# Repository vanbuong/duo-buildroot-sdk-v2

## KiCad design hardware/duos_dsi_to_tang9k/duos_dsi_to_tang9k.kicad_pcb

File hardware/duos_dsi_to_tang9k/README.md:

# Duo S MIPI DSI -> Tang Nano 9K

Generated by `gen_project.py` (re-run to regenerate). Open `duos_dsi_to_tang9k.kicad_pro` in KiCad 7+.
Network diagram: `dphy_full_lp_network.png`.

## Connectors
- **J1** = Duo S CON26A (2x13). pair0=D0 (1/3), pair1=D1 (2/4), pair2=CLK (7/9); D2/D3 unused.
- **J2** mirrors Tang Nano 9K header J6 (pin n = pin n), **J3** mirrors header J5.

| Signal | Tang pin | Header pin | Bank/IO |
|---|---|---|---|
| HS_CK_P / N | 80 / 79 | J6-8 / J6-9 | IOT12A/B, 1.8 V LVDS |
| HS_D0_P / N | 82 / 81 | J6-6 / J6-7 | IOT11A/B, 1.8 V LVDS |
| HS_D1_P / N | 84 / 83 | J6-4 / J6-5 | IOT10A/B, 1.8 V LVDS |
| LP_D0_P | 85 | J6-3 | IOT8B, 1.8 V LVCMOS |
| LP_CK_P (via level shifter) | 25 | J5-5 | IOB8A, 3.3 V |
| LP_D1_P (via level shifter) | 26 | J5-6 | IOB8B, 3.3 V |

J2 pin 23 = GND and pin 24 = 3V3 are used for the level shifters and VCM bias.

## Receive network (per lane)
- 2x50R + 100nF split termination: 100R differential at HS, DC-open so LP levels are not loaded.
- HS AC-coupled (100nF) to the LVDS pair, biased to VCM 0.9 V (27k/10k divider from 3V3).
- 470R LP tap from DSI_x_P. CK and D1 go through SN74AUP1T17 (3.3 V supply) to the 3.3 V pins; D0 goes straight to pin 85.
- 2-layer, 0.8 mm, GND pour on B.Cu; `DSI_*`/`HS_*` are in net class MIPI_DPHY_100R (0.25/0.2 mm starting values - verify).

## Must verify before fab
1. SN74AUP1T17: check the datasheet that VT+ (max) at VCC=3.3 V is below the D-PHY LP-high level (>= 0.88 V RX spec). Pick another low-threshold part if not.
2. `ROW_PITCH` (J2<->J3 spacing, 17.78 mm assumed) and pin-1 orientation vs your Tang Nano 9K. Use female sockets.
3. Confirm in the Gowin pin list that IOT10/11/12 A/B are true LVDS _T/_C pairs and that LVDS input at 1.8 V VCCO with 0.9 V common mode is allowed.
4. Lane map matches the SDK 2-lane panel config {LANE_0, LANE_1, LANE_CLK}; swap `lane_pn_swap` in `cvi_mpi/component/panel/cv181x/*.h` if routing ends up crossed.
5. Generated without KiCad available: open, run ERC/DRC (expect 3V3/GND power-flag warnings), route, re-save.

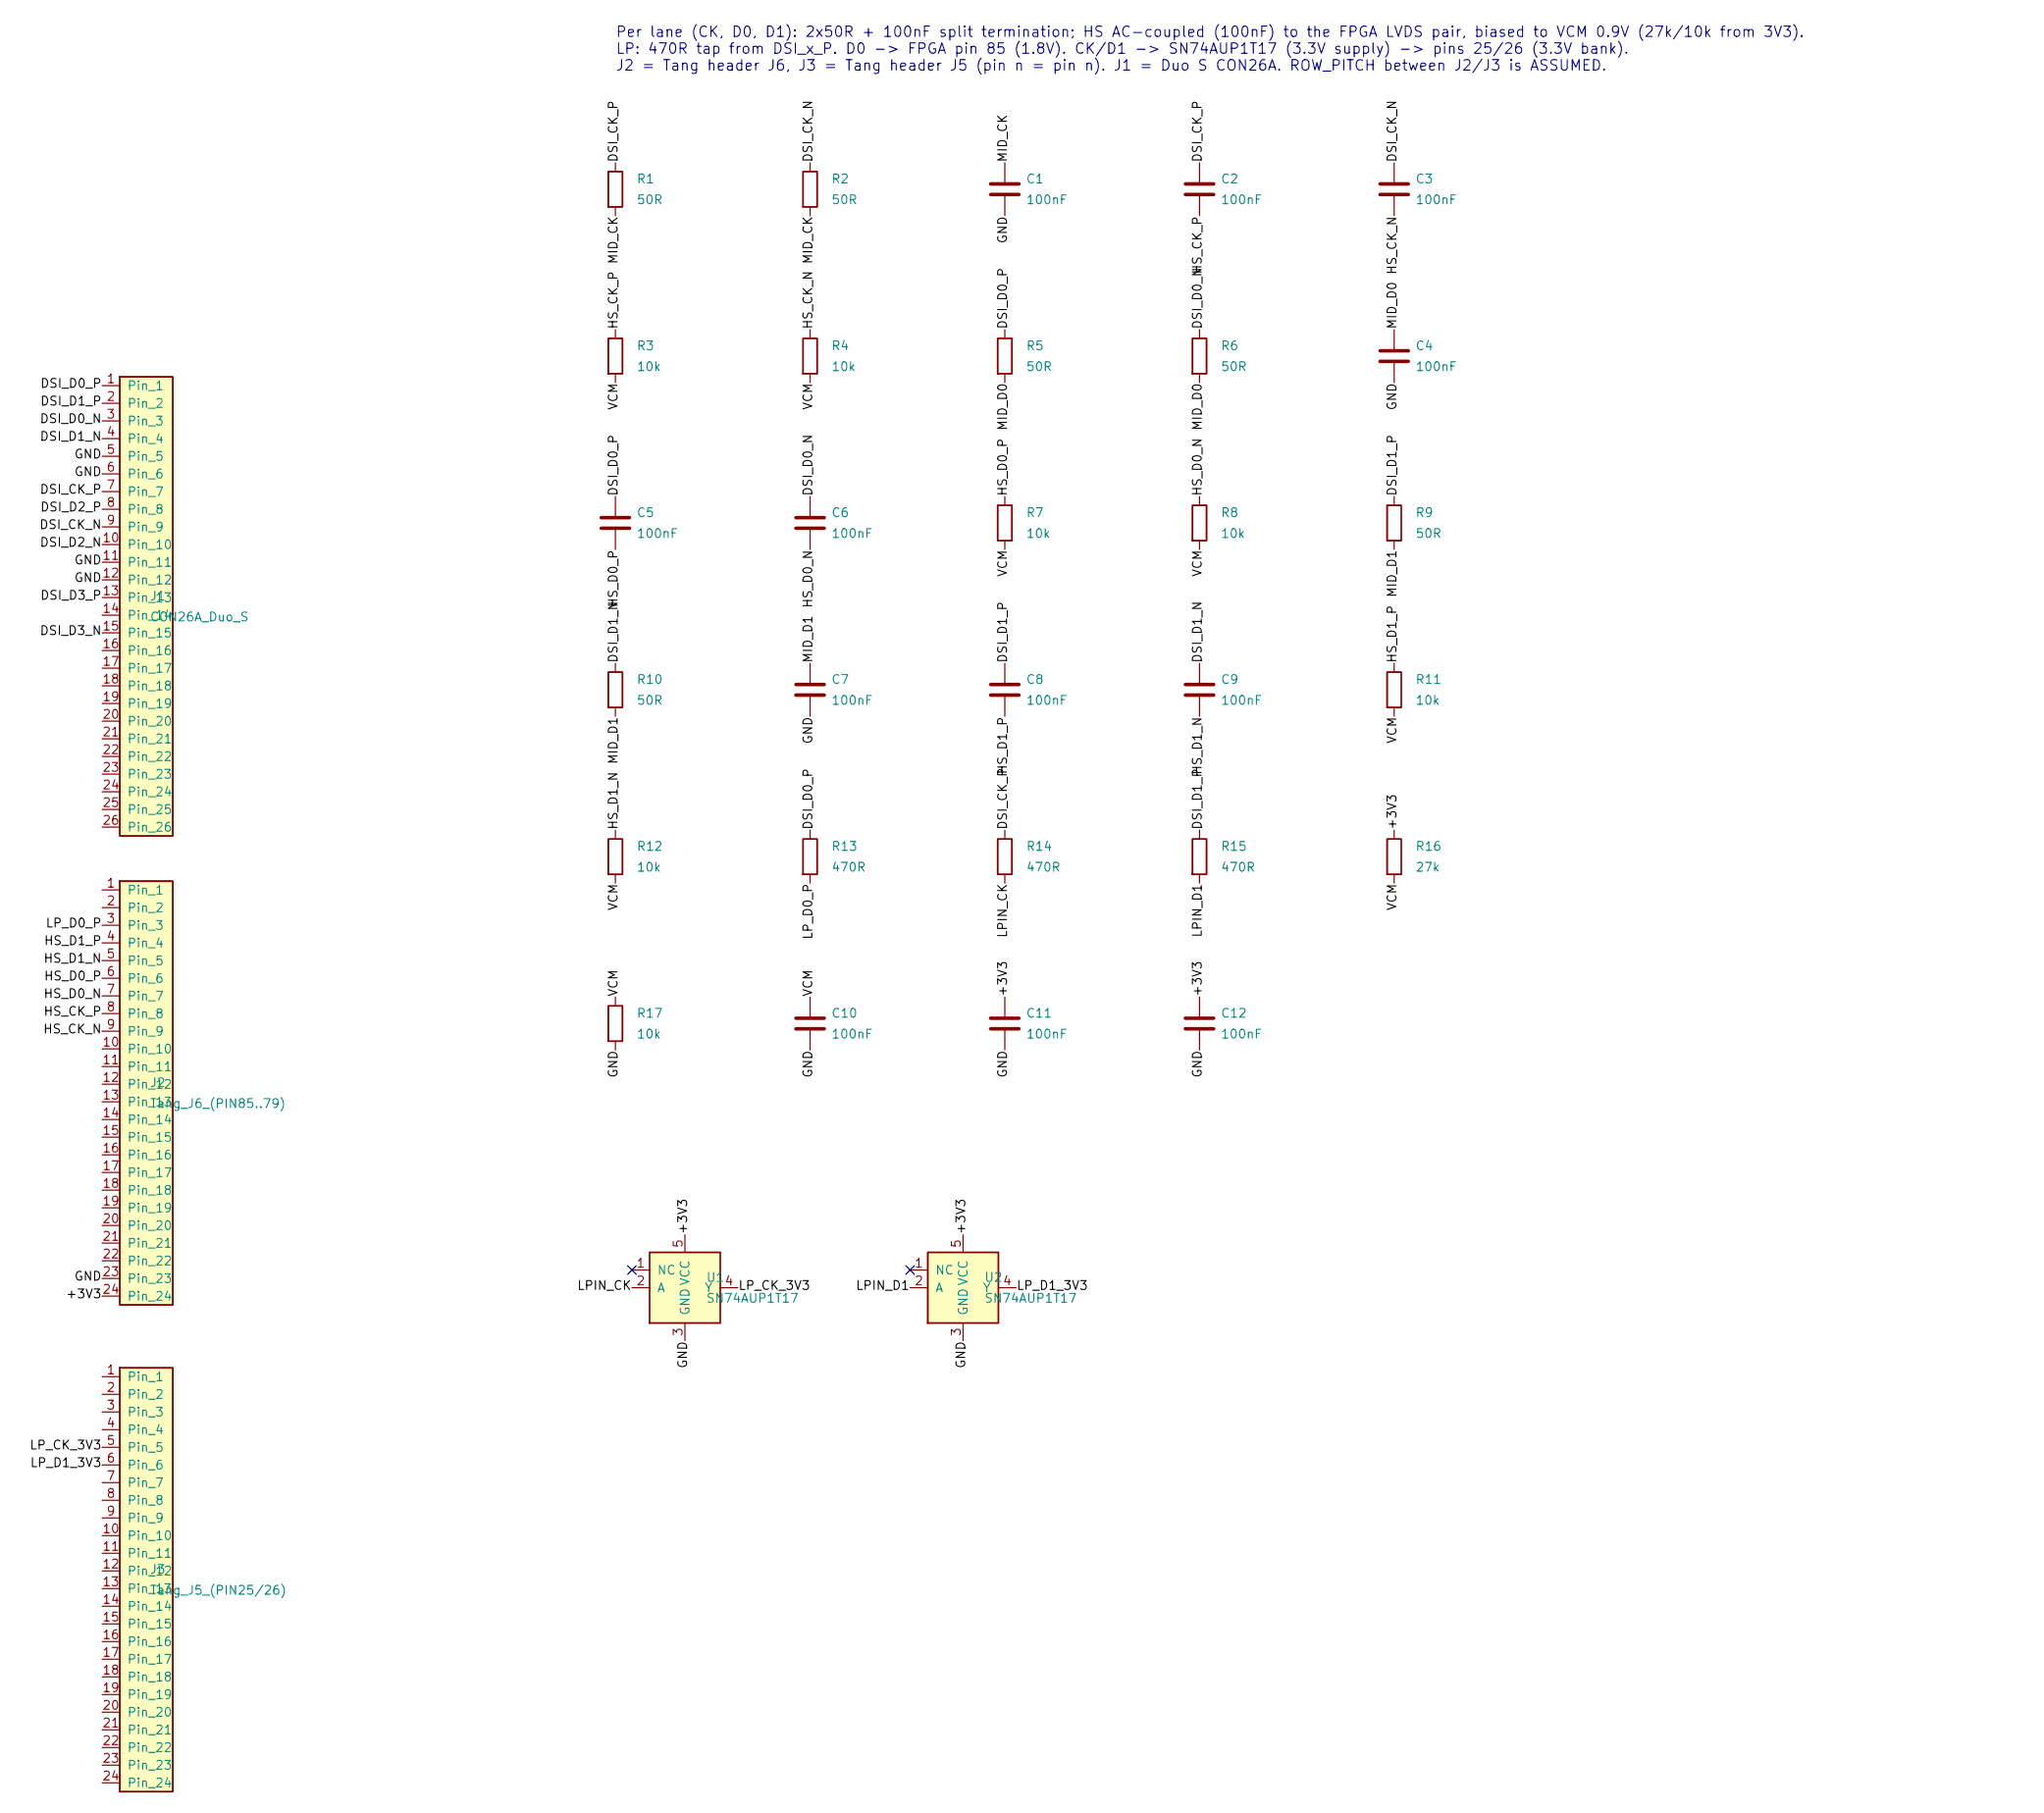
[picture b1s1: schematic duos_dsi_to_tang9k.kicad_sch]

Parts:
C1, C2, C3, C4, C5, C6, C7, C8, C9, C10, C11, C12: 100nF; C_0402_1005Metric
J1: CON26A_Duo_S; PinHeader_2x13_P2.54mm_Vertical
J2: Tang_J6_(PIN85..79); PinHeader_1x24_P2.54mm_Vertical
J3: Tang_J5_(PIN25/26); PinHeader_1x24_P2.54mm_Vertical
R1, R2, R5, R6, R9, R10: 50R; R_0402_1005Metric
R3, R4, R7, R8, R11, R12, R17: 10k; R_0402_1005Metric
R13, R14, R15: 470R; R_0402_1005Metric
R16: 27k; R_0402_1005Metric
U1, U2: SN74AUP1T17; SOT-23-5

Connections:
+3V3: C11.1, C12.1, J2.24, R16.1, U1.5 (VCC), U2.5 (VCC)
DSI_CK_N: C3.1, J1.9, R2.1
DSI_CK_P: C2.1, J1.7, R1.1, R14.1
DSI_D0_N: C6.1, J1.3, R6.1
DSI_D0_P: C5.1, J1.1, R5.1, R13.1
DSI_D1_N: C9.1, J1.4, R10.1
DSI_D1_P: C8.1, J1.2, R9.1, R15.1
DSI_D2_N: J1.10
DSI_D2_P: J1.8
DSI_D3_N: J1.15
DSI_D3_P: J1.13
GND: C1.2, C4.2, C7.2, C10.2, C11.2, C12.2, J1.5, J1.6, J1.11, J1.12, J2.23, R17.2, U1.3 (GND), U2.3 (GND)
HS_CK_N: C3.2, J2.9, R4.1
HS_CK_P: C2.2, J2.8, R3.1
HS_D0_N: C6.2, J2.7, R8.1
HS_D0_P: C5.2, J2.6, R7.1
HS_D1_N: C9.2, J2.5, R12.1
HS_D1_P: C8.2, J2.4, R11.1
LPIN_CK: R14.2, U1.2 (A)
LPIN_D1: R15.2, U2.2 (A)
LP_CK_3V3: J3.5, U1.4 (Y)
LP_D0_P: J2.3, R13.2
LP_D1_3V3: J3.6, U2.4 (Y)
MID_CK: C1.1, R1.2, R2.2
MID_D0: C4.1, R5.2, R6.2
MID_D1: C7.1, R9.2, R10.2
VCM: C10.1, R3.2, R4.2, R7.2, R8.2, R11.2, R12.2, R16.2, R17.1

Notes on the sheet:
Per lane (CK, D0, D1): 2x50R + 100nF split termination; HS AC-coupled (100nF) to the FPGA LVDS pair, biased to VCM 0.9V (27k/10k from 3V3). LP: 470R tap from DSI_x_P. D0 -> FPGA pin 85 (1.8V). CK/D1 -> SN74AUP1T17 (3.3V supply) -> pins 25/26 (3.3V bank). J2 = Tang header J6, J3 = Tang header J5 (pi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

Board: 2 copper layers, 34 parts (0 on the bottom side), 23 nets, no tracks yet.

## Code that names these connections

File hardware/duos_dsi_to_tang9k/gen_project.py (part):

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        l[k - 1] = v
    return l
# J2 mirrors Tang Nano 9K header J6 (pin n = J6 pin n).  A half of each IOT pair = P (true), B = N.
J2 = hdr24({3: "LP_D0_P",                 # PIN85 IOT8B  (1.8V, single-ended)
            4: "HS_D1_P", 5: "HS_D1_N",   # PIN84/83 IOT10A/B
            6: "HS_D0_P", 7: "HS_D0_N",   # PIN82/81 IOT11A/B
            8: "HS_CK_P", 9: "HS_CK_N",   # PIN80/79 IOT12A/B
            23: G, 24: "+3V3"})
# J3 mirrors Tang Nano 9K header J5 (pin n = J5 pin n)
J3 = hdr24({5: "LP_CK_3V3",               # PIN25 IOB8A
            6: "LP_D1_3V3"})              # PIN26 IOB8B
ROW_PITCH = 17.78   # ASSUMED distance between the two Tang header rows (0.7in) - measure your board

# 2-pin parts: (kind, value, netA, netB)
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              ("C", "100nF", f"DSI_{x}_P", f"HS_{x}_P"), ("C", "100nF", f"DSI_{x}_N", f"HS_{x}_N"),
              ("R", "10k", f"HS_{x}_P", "VCM"), ("R", "10k", f"HS_{x}_N", "VCM")]
PARTS += [("R", "470R", "DSI_D0_P", "LP_D0_P"),
          ("R", "470R", "DSI_CK_P", "LPIN_CK"), ("R", "470R", "DSI_D1_P", "LPIN_D1"),
          ("R", "27k", "+3V3", "VCM"), ("R", "10k", "VCM", G), ("C", "100nF", "VCM", G),
          ("C", "100nF", "+3V3", G), ("C", "100nF", "+3V3", G)]
# ICs: SN74AUP1T17 (SOT-23-5): 1 NC, 2 A, 3 GND, 4 Y, 5 VCC
ICS = [("U1", {2: "LPIN_CK", 3: G, 4: "LP_CK_3V3", 5: "+3V3"}),
       ("U2", {2: "LPIN_D1", 3: G, 4: "LP_D1_3V3", 5: "+3V3"})]

cnt = {"R": 0, "C": 0}
PL = []   # (ref, kind, value, a, b)
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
